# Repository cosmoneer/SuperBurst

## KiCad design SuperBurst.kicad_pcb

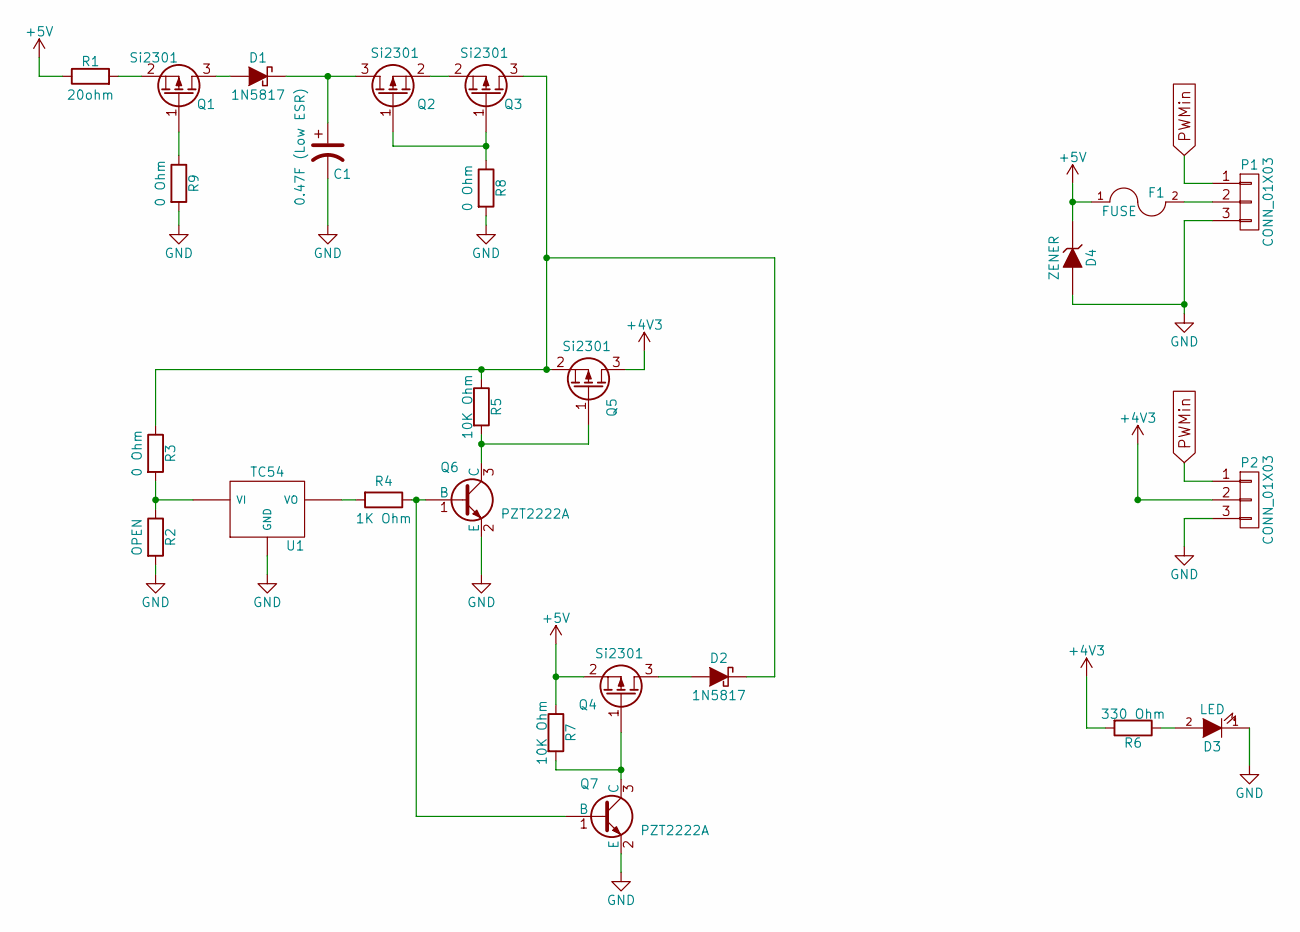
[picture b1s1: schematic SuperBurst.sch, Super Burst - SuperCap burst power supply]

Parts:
C1: 0.47F (Low ESR); CP5.5V1.5F
D1, D2: 1N5817; SMA-SMB_Universal_Handsoldering
D3: LED; R_0805_HandSoldering
D4: ZENER; SMA-SMB_Universal_Handsoldering
F1: FUSE; R_0805_HandSoldering
P1: CONN_01X03; Pin_Header_Angled_1x03
P2: CONN_01X03; Pin_Header_Angled_1x03B
Q1, Q2, Q3, Q4, Q5: Si2301; SOT-23_Handsoldering
Q6, Q7: PZT2222A; SOT-23_Handsoldering
R1: 20ohm; R_2512_HandSoldering
R2: OPEN; R_0805_HandSoldering
R3, R8, R9: 0 Ohm; R_0805_HandSoldering
R4: 1K Ohm; R_0805_HandSoldering
R5, R7: 10K Ohm; R_0805_HandSoldering
R6: 330 Ohm; R_0805_HandSoldering
U1: TC54; SOT-23_Handsoldering

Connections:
+4V3: P2.2, Q5.3 (D), R6.2
+5V: D4.1 (K), F1.1, Q4.2 (S), R1.1, R7.1
GND: C1.2, D3.1 (K), D4.2 (A), P1.3, P2.3, Q6.2 (E), Q7.2 (E), R2.2, R8.2, R9.2, U1.2 (GND)
unnamed: C1.1, D1.1 (K), Q2.3 (D)
unnamed: D1.2 (A), Q1.3 (D)
unnamed: D2.1 (K), Q3.3 (D), Q5.2 (S), R3.1, R5.1
unnamed: D2.2 (A), Q4.3 (D)
unnamed: D3.2 (A), R6.1
unnamed: F1.2, P1.2
unnamed: Q1.1 (G), R9.1
unnamed: Q1.2 (S), R1.2
unnamed: Q2.1 (G), Q3.1 (G), R8.1
unnamed: Q2.2 (S), Q3.2 (S)
unnamed: Q4.1 (G), Q7.3 (C), R7.2
unnamed: Q5.1 (G), Q6.3 (C), R5.2
unnamed: Q6.1 (B), Q7.1 (B), R4.1
unnamed: R2.1, R3.2, U1.3 (VI)
unnamed: R4.2, U1.1 (VO)
PWMin: P1.1, P2.1

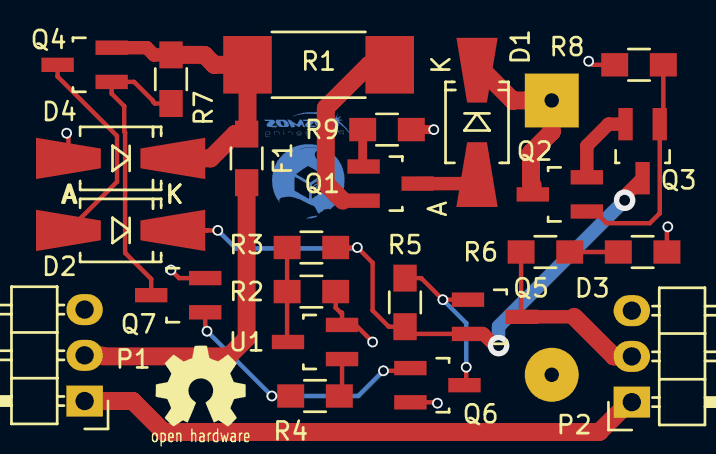
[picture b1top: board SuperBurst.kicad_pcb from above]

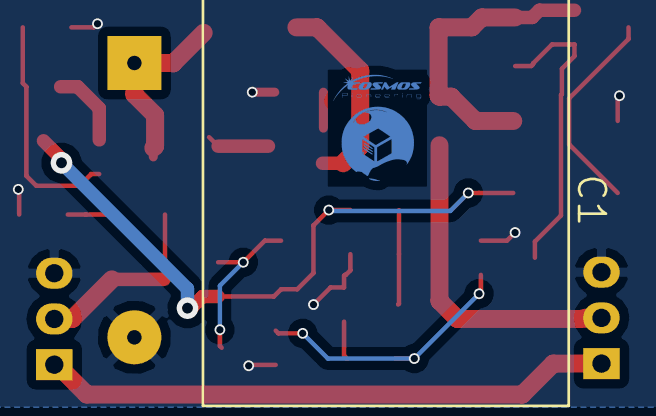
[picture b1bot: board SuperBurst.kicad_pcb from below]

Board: 2 copper layers, 25 parts (2 on the bottom side), 19 nets.

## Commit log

2016-09-19 :confetti_ball: Added .gitattributes & .gitignore files
2016-09-19 1.5F Supercap Design
    Servo/Gyro motor burst power supply w/ .7 voltage drop to support 4.3v
    supply requirement for single lipo cell ESCs.
2016-09-23 Low ESR supercap with voltage detector
    Advanced discrete component circuit that charges the supercap, then via
    mosfets as switches, exposes the charged supercap to downstream loads.
2017-03-23 First Load
    Initial load of the board

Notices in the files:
SuperBurst.sch:
Released for free under a creative commons attribution 2.5 license
